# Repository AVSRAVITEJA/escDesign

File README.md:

# escDesign
This file consists the schematic of an ESC and its PCB design in KICAD 
The electronic speed controller (ESC) is an essential part of an electric propulsion system's hardware. It acts like the brain of the system by telling the motor how fast to go based on data signals it receives from the flight controller. ESCs are available for either brushed (DC) or brushless (AC) motors. Brushed motors are most commonly used in toy-class planes, multicopters, rovers, boats, and balance bots. Most other larger vehicles use brushless speed controllers.
This repo consists the KICAD files of an ESC required to control the motors of a quadcopter

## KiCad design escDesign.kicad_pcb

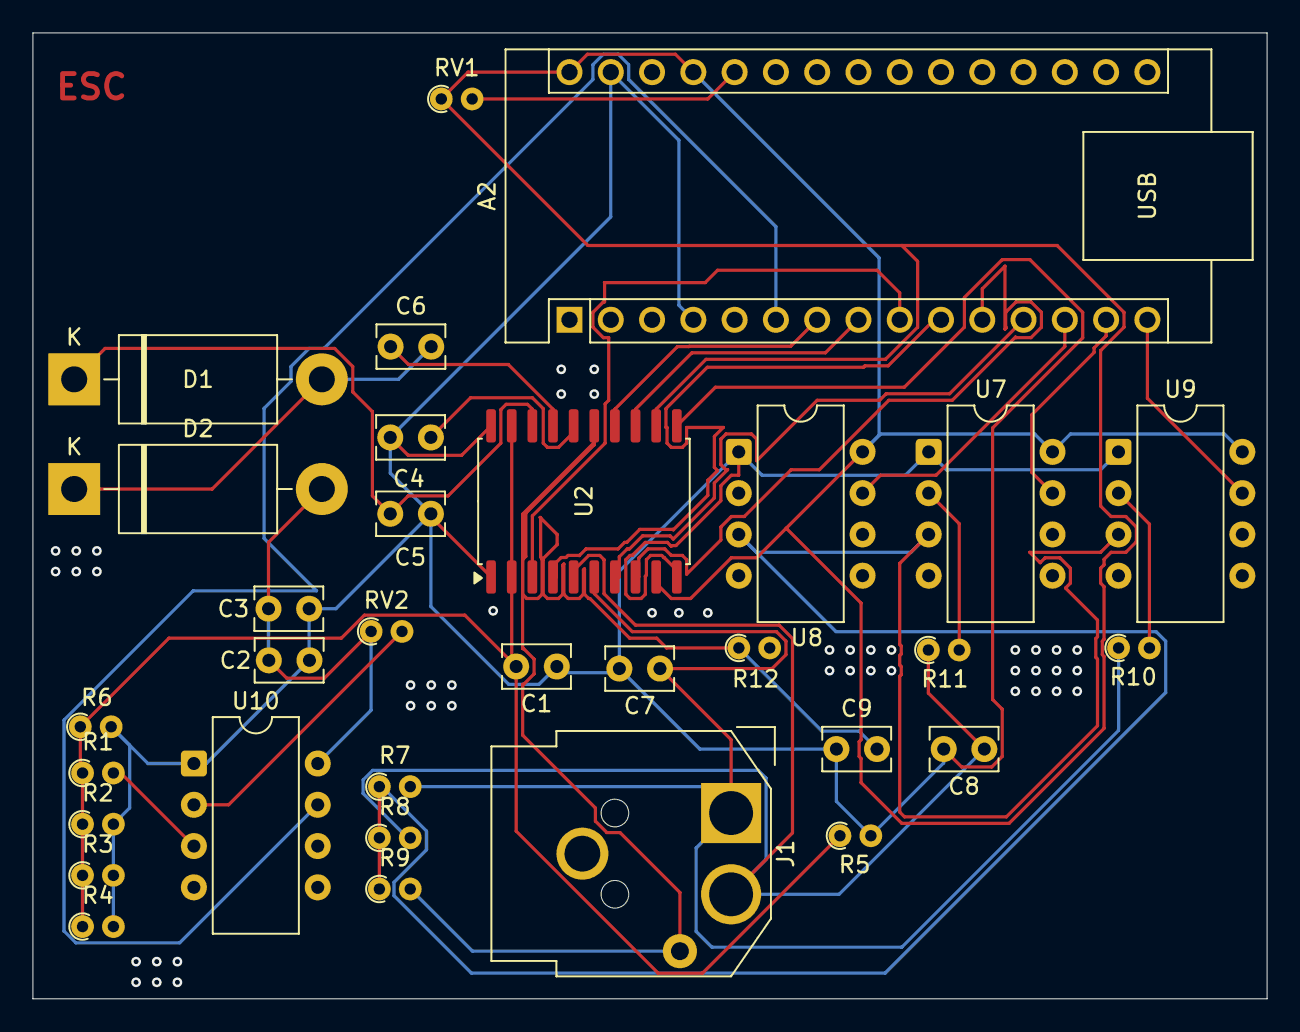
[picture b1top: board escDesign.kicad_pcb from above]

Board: 2 copper layers, 75.9 x 59.4 mm, 32 parts (0 on the bottom side), 27 nets.

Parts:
A2: Arduino_Nano_v2.x; Arduino_Nano
C1, C7, C8, C9: 470nF; C_Rect_L4.0mm_W2.5mm_P2.50mm
C2, C4: 1uF; C_Rect_L4.0mm_W2.5mm_P2.50mm
C3: 100nF; C_Rect_L4.0mm_W2.5mm_P2.50mm
C5: 220nF; C_Rect_L4.0mm_W2.5mm_P2.50mm
C6: 10nF; C_Rect_L4.0mm_W2.5mm_P2.50mm
D1, D2: D; D_DO-201AD_P15.24mm_Horizontal
J1: CUI_PD-30
R1, R10, R11, R12: 1k; R_Axial_DIN0204_L3.6mm_D1.6mm_P1.90mm_Vertical
R2, R3, R4, R5, R6: 1; R_Axial_DIN0204_L3.6mm_D1.6mm_P1.90mm_Vertical
R7, R8, R9: 10k; R_Axial_DIN0204_L3.6mm_D1.6mm_P1.90mm_Vertical
RV1, RV2: 10k; R_Axial_DIN0204_L3.6mm_D1.6mm_P1.90mm_Vertical
U2: SOIC-20W_7.5x12.8mm_P1.27mm
U7, U8, U9, U10: LM311; CERDIP-8_W7.62mm_SideBrazed

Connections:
+5V: A2.27 (+5V), A2.30 (VIN), C2.1, C3.1, D2.2 (A), RV1.1, RV2.1, U2.9 (Vs), U2.12 (Vs), U7.8 (V+), U8.8 (V+), U9.8 (V+), U10.8 (V+)
/D4: A2.7 (D4), U2.14 (IN3)
/D5: A2.8 (D5), U2.13 (EN3)
/D6: A2.9 (D6), U2.3 (EN2)
/D7: A2.10 (D7), U2.4 (IN2)
/D8: A2.11 (D8), U2.8 (EN1)
/D9: A2.12 (D9), U2.7 (IN1)
GND: A2.4 (GND), A2.29 (GND), C1.2, C2.2, C3.2, C4.2, C5.2, C7.1, C8.1, C9.1, R2.2, R3.2, R4.2, R5.2, R6.2, U2.1 (GND), U2.10 (GND), U2.11 (GND), U2.20 (GND), U7.1 (GND), U8.1 (GND), U9.1 (GND), U10.1 (GND)
unnamed: A2.26 (A7), RV1.2
unnamed: A2.6 (D3), U10.7
unnamed: A2.13 (D10), U8.7
unnamed: A2.14 (D11), U7.7
unnamed: A2.15 (D12), U9.7
unnamed: C6.2, D1.2 (A), D2.1 (K)
unnamed: C5.1, D1.1 (K), U2.18 (VBOOT)
unnamed: C7.2, J1.1, R7.2, R10.1, U2.6 (OUT1)
unnamed: C8.2, J1.2, R8.2, R11.1, U2.5 (OUT2)
unnamed: C9.2, J1.3, R9.2, R12.1, U2.15 (OUT3)
unnamed: C1.1, R1.1, R2.1, R3.1, R4.1, R5.1, R6.1, U2.2 (SENSE1), U2.19 (SENSE2)
unnamed: C6.1, U2.17 (VCP)
unnamed: C4.1, U2.16 (VREF)
unnamed: R11.2, U7.2 (+)
unnamed: R7.1, R8.1, R9.1, U7.3 (-), U8.3 (-), U9.3 (-)
unnamed: R12.2, U8.2 (+)
unnamed: R10.2, U9.2 (+)
unnamed: RV2.2, U10.2 (+)
unnamed: R1.2, U10.3 (-)
